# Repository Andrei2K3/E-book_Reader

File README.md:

# OpenBook Project - README

This repository contains the hardware, manufacturing, mechanical, and documentation files for **OpenBook**, a low-cost, open-source e-book reader built around the **ESP32-C6** microcontroller.

---

## Overview

The OpenBook is a low-power, open-source e-book reader designed around the ESP32-C6 microcontroller. Featuring Wi-Fi 6 and Bluetooth LE, it uses a large 7.5-inch e-paper display to achieve excellent readability and battery performance.

This document includes the system block diagram, hardware pinout, BOM, component links, design log, and licensing.

---

## System Block Diagram

---

## Bill of Materials (BOM)

| Name of component | Device                                       | Check Prices                                                                                                | DataSheet                                                                                                 |
|-------------------|----------------------------------------------|-----------------------------------------------------------------------------------------------------------------|---------------------------------------------------------------------------------------------------------------|
| U1                | W25Q512JVEIQ                                 | https://www.snapeda.com/parts/W25Q512JVEIQ/Winbond+Electronics/view-part/?ref=eda                             | https://www.snapeda.com/parts/W25Q512JVEIQ/Winbond+Electronics/view-part/?ref=eda                             |
| U2                | ESP32-C6-WROOM-1-N8                          | https://www.snapeda.com/parts/ESP32-C6-WROOM-1-N8/Espressif+Systems/view-part/?ref=eda                        | https://www.snapeda.com/parts/ESP32-C6-WROOM-1-N8/Espressif+Systems/view-part/?ref=eda                        |
| U3                | DS3231SN#                                    | https://www.snapeda.com/parts/DS3231SN%23/Analog+Devices/view-part/?ref=eda                                   | https://www.snapeda.com/parts/DS3231SN%23/Analog+Devices/view-part/?ref=eda                                   |
| U4                | MAX17048G+T10                                | https://www.snapeda.com/parts/MAX17048G+T10/Analog+Devices/view-part/?ref=eda                                 | https://www.snapeda.com/parts/MAX17048G+T10/Analog+Devices/view-part/?ref=eda                                 |
| U5                | ESP32_WROVER_SPARKFUN-IC-POWER_MCP73831      | https://eu.mouser.com/ProductDetail/Microchip-Technology/MCP73831T-2ACI-OT?qs=yUQqVecv4qvbBQBGbHx0Mw%3D%3Dcf   | https://eu.mouser.com/ProductDetail/Microchip-Technology/MCP73831T-2ACI-OT?qs=yUQqVecv4qvbBQBGbHx0Mw%3D%3Dcf   |
| BOOT_BUTTON       | BUTTON_CUSYOMV1                             | https://industry.panasonic.com/global/en/products/control/switch/light-touch/number/evqpuj02k                  | https://industry.panasonic.com/global/en/products/control/switch/light-touch/number/evqpuj02k                  |
| CHANGE_BUTTON     | BUTTON_CUSYOMV1                             | https://industry.panasonic.com/global/en/products/control/switch-light-touch/number/evqpuj02k                  | https://industry.panasonic.com/global/en/products/control/switch-light-touch/number/evqpuj02k                  |
| RESET_BUTTON      | BUTTON_CUSYOMV1                             | https://industry.panasonic.com/global/en/products/control/switch/light-touch/number/evqpuj02k                  | https://industry.panasonic.com/global/en/products/control/switch/light-touch/number/evqpuj02k                  |
| Q1                | ESP32_WROVER_SPARKFUN-DISCRETESEMI_MOSFET_...| https://componentsearchengine.com/part-view/DMG2305UX-7/Diodes%20Incorporated                                  | https://componentsearchengine.com/part-view/DMG2305UX-7/Diodes%20Incorporated                                  |
| Q2                | ESP32_WROVER_SPARKFUN-DISCRETESEMI_MOSFET_...| https://componentsearchengine.com/part-view/DMG2305UX-7/Diodes%20Incorporated                                  | https://componentsearchengine.com/part-view/DMG2305UX-7/Diodes%20Incorporated                                  |
| Q3                | D8                                           | https://componentsearchengine.com/part-view/SI1308EDL-T1-GE3/Vishay                                           | https://componentsearchengine.com/part-view/SI1308EDL-T1-GE3/Vishay                                           |
| PFMF.050.1        | ESP32C6_VARISTORCN1812                       | https://www.mouser.co.uk/ProductDetail/EPCOS-TDK/B72520T0350K062?qs=dEfas%2FXlABIszF52uu7vrg%3D%3D              | https://www.mouser.co.uk/ProductDetail/EPCOS-TDK/B72520T0350K062?qs=dEfas%2FXlABIszF52uu7vrg%3D%3D              |
| IC1               | BD5229G-TR                                   | https://componentsearchengine.com/part-view/BD5229G-TR/ROHM%20Semiconductor                                    | https://componentsearchengine.com/part-view/BD5229G-TR/ROHM%20Semiconductor                                    |
| IC4               | XC6220A331MR-G                               | https://componentsearchengine.com/part-view/XC6220A331MR-G/Torex                                              | https://componentsearchengine.com/part-view/XC6220A331MR-G/Torex                                              |
| J1                | FH34SRJ-24S-0.5SH_99_                        | https://componentsearchengine.com/part-view/XC6220A331MR-G/Torex                                              | https://componentsearchengine.com/part-view/XC6220A331MR-G/Torex                                              |
| J2                | SAMACSYS_PARTS_USB4110-GF-A                  | https://componentsearchengine.com/part-view/USB4110-GF-A/GCT%20(GLOBAL%20CONNECTOR%20TECHNOLOGY               | https://componentsearchengine.com/part-view/USB4110-GF-A/GCT%20(GLOBAL%20CONNECTOR%20TECHNOLOGY               |
| J3                | QWIIC_CONNECTORJS-1MM                        | https://componentsearchengine.com/part-view/USB4110-GF-A/GCT%20(GLOBAL%20CONNECTOR%20TECHNOLOGY               | https://componentsearchengine.com/part-view/USB4110-GF-A/GCT%20(GLOBAL%20CONNECTOR%20TECHNOLOGY               |
| J4                | 112A-TAAR-R03_ATTEND                         | https://store.comet.srl.ro/Catalogue/Product/43497/                                                            | https://store.comet.srl.ro/Catalogue/Product/43497/                                                            |
| L1                | 744043680IND_4828-WE-TPC_WRE                 | https://eu.mouser.com/ProductDetail/Wurth-Elektronik/744043680?qs=PGXP4M47uW6VkZq%252BkzjrHA%3D%3D               | https://eu.mouser.com/ProductDetail/Wurth-Elektronik/744043680?qs=PGXP4M47uW6VkZq%252BkzjrHA%3D%3D               |
| SENSOR2           | ESP32_WROVER_BME680_BME680                   | https://www.snapeda.com/parts/BME680/Bosch/view-part/?welcome=home                                            | https://www.snapeda.com/parts/BME680/Bosch/view-part/?welcome=home                                            |
| SJ1              | SJ                                           | https://grabcad.com/library/solder-jumpers-1                                                                   | https://grabcad.com/library/solder-jumpers-1                                                                   |
| C1                | ESP32_WROVER_EAGLE-LTSPICE_CC0402            | https://industry.panasonic.com/global/en/products/control/switch/light-touch/number/evqpuj02k                  | https://industry.panasonic.com/global/en/products/control/switch/light-touch/number/evqpuj02k                  |
| C1_BAT            | ESP32_WROVER_EAGLE-LTSPICE_CC0402            | https://industry.panasonic.com/global/en/products/control/switch/light-touch/number/evqpuj02k                  | https://industry.panasonic.com/global/en/products/control/switch/light-touch/number/evqpuj02k                  |
| C1_BAT1           | EAGLE-LTSPICE_CC0402                         | https://industry.panasonic.com/global/en/products/control/switch/light-touch/number/evqpuj02k                  | https://industry.panasonic.com/global/en/products/control/switch/light-touch/number/evqpuj02k                  |
| C1_BAT2           | EAGLE-LTSPICE_CC0402                         | https://industry.panasonic.com/global/en/products/control/switch/light-touch/number/evqpuj02k                  | https://industry.panasonic.com/global/en/products/control/switch/light-touch/number/evqpuj02k                  |
| C2                | ESP32_WROVER_EAGLE-LTSPICE_CC0402            | https://industry.panasonic.com/global/en/products/control/switch/light-touch/number/evqpuj02k                  | https://industry.panasonic.com/global/en/products/control/switch/light-touch/number/evqpuj02k                  |
| C2_BAT\           | ESP32_WROVER_EAGLE-LTSPICE_CC0402            | https://industry.panasonic.com/global/en/products/control/switch/light-touch/number/evqpuj02k                  | https://industry.panasonic.com/global/en/products/control/switch/light-touch/number/evqpuj02k                  |
| C3                | RCL_CPOL-EUCT3528                            | https://industry.panasonic.com/global/en/products/control/switch/light-touch/number/evqpuj02k                  | https://industry.panasonic.com/global/en/products/control/switch/light-touch/number/evqpuj02k                  |
| C4                | ESP32_WROVER_EAGLE-LTSPICE_CC0402            | https://industry.panasonic.com/global/en/products/control/switch/light-touch/number/evqpuj02k                  | https://industry.panasonic.com/global/en/products/control/switch/light-touch/number/evqpuj02k                  |
| C4_USB            | ESP32_WROVER_EAGLE-LTSPICE_CC0402            | https://industry.panasonic.com/global/en/products/control/switch/light-touch/number/evqpuj02k                  | https://industry.panasonic.com/global/en/products/control/switch/light-touch/number/evqpuj02k                  |
| C5                | ESP32_WROVER_EAGLE-LTSPICE_CC0402            | https://industry.panasonic.com/global/en/products/control/switch/light-touch/number/evqpuj02k                  | https://industry.panasonic.com/global/en/products/control/switch/light-touch/number/evqpuj02k                  |
| C5_USB            | ESP32_WROVER_EAGLE-LTSPICE_CC0402            | https://industry.panasonic.com/global/en/products/control/switch/light-touch/number/evqpuj02k                  | https://industry.panasonic.com/global/en/products/control/switch/light-touch/number/evqpuj02k                  |
| C6                | ESP32_WROVER_EAGLE-LTSPICE_CC0402            | https://industry.panasonic.com/global/en/products/control/switch/light-touch/number/evqpuj02k                  | https://industry.panasonic.com/global/en/products/control/switch/light-touch/number/evqpuj02k                  |
| C7                | ESP32_WROVER_EAGLE-LTSPICE_CC0402            | https://industry.panasonic.com/global/en/products/control/switch/light-touch/number/evqpuj02k                  | https://industry.panasonic.com/global/en/products/control/switch/light-touch/number/evqpuj02k                  |
| C8                | ESP32_WROVER_EAGLE-LTSPICE_CC0402            | https://industry.panasonic.com/global/en/products/control/switch/light-touch/number/evqpuj02k                  | https://industry.panasonic.com/global/en/products/control/switch/light-touch/number/evqpuj02k                  |
| C9                | EAGLE-LTSPICE_CC0402                         | https://industry.panasonic.com/global/en/products/control/switch/light-touch/number/evqpuj02k                  | https://industry.panasonic.com/global/en/products/control/switch/light-touch/number/evqpuj02k                  |
| C10               | ESP32_WROVER_EAGLE-LTSPICE_CC0402            | https://industry.panasonic.com/global/en/products/control/switch/light-touch/number/evqpuj02k                  | https://industry.panasonic.com/global/en/products/control/switch/light-touch/number/evqpuj02k                  |
| C10_SUPERCAP      | CPH3225A                                     | https://www.snapeda.com/parts/CPH3225A/Seiko+Instruments/view-part/?ref=eda                                   | https://www.snapeda.com/parts/CPH3225A/Seiko+Instruments/view-part/?ref=eda                                   |
| CHG_LED           | ADAFRUIT_LEDCHIP-LED0603                     | https://www.snapeda.com/parts/KP-1608SURCK/Kingbright/view-part/?ref=search&t=LED%200603                       | https://www.snapeda.com/parts/KP-1608SURCK/Kingbright/view-part/?ref=search&t=LED%200603                       |
| C_DELAY           | ESP32_WROVER_EAGLE-LTSPICE_CC0402            | https://industry.panasonic.com/global/en/products/control/switch/light-touch/number/evqpuj02k                  | https://industry.panasonic.com/global/en/products/control/switch/light-touch/number/evqpuj02k                  |
| D1                | USBLC6-2SC6Y                                 | https://www.snapeda.com/parts/USBLC6-2SC6Y/STMicroelectronics/view-part/?ref=eda                              | https://www.snapeda.com/parts/USBLC6-2SC6Y/STMicroelectronics/view-part/?ref=eda                              |
| D2                | ESP32_WROVER_AVX---SD0805S020S1R0_AVX_...    | https://eu.mouser.com/ProductDetail/KYOCERA-AVX/SD0805S020S1R0?qs=jCA%252BPfw4LHbpkAoSnwrdjw%3D%3D              | http://datasheets.avx.com/schottky.pdf                                                                         |
| D3                | MBR0530                                      | https://eu.mouser.com/ProductDetail/KYOCERA-AVX/SD0805S020S1R0?qs=jCA%252BPfw4LHbpkAoSnwrdjw%3D%3D              | https://eu.mouser.com/ProductDetail/KYOCERA-AVX/SD0805S020S1R0?qs=jCA%252BPfw4LHbpkAoSnwrdjw%3D%3D              |
| D4                | MBR0530                                      | https://www.snapeda.com/parts/MBR0530/Onsemi/view-part/?ref=eda                                                | https://www.snapeda.com/parts/MBR0530/Onsemi/view-part/?ref=eda                                                |
| D5                | MBR0530                                      | https://www.snapeda.com/parts/MBR0530/Onsemi/view-part/?ref=eda                                                | https://www.snapeda.com/parts/MBR0530/Onsemi/view-part/?ref=eda                                                |
| D6                | PGB1010603MR                                 | https://www.snapeda.com/parts/PGB1010603MR/Littelfuse/view-part/?ref=eda                                      | https://www.snapeda.com/parts/PGB1010603MR/Littelfuse/view-part/?ref=eda                                      |
| D7                | ESP32_WROVER_AVX---SD0805S020S1R0_AVX_...    | https://eu.mouser.com/ProductDetail/KYOCERA-AVX/SD0805S020S1R0?qs=jCA%252BPfw4LHbpkAoSnwrdjw%3D%3D              | http://datasheets.avx.com/schottky.pdf                                                                         |
| D8                | PGB1010603MR                                 | https://www.snapeda.com/parts/PGB1010603MR/Littelfuse/view-part/?ref=eda                                      | https://www.snapeda.com/parts/PGB1010603MR/Littelfuse/view-part/?ref=eda                                      |
| D9                | PGB1010603MR                                 | https://www.snapeda.com/parts/PGB1010603MR/Littelfuse/view-part/?ref=eda                                      | https://www.snapeda.com/parts/PGB1010603MR/Littelfuse/view-part/?ref=eda                                      |
| D10               | PGB1010603MR                                 | https://www.snapeda.com/parts/PGB1010603MR/Littelfuse/view-part/?ref=eda                                      | https://www.snapeda.com/parts/PGB1010603MR/Littelfuse/view-part/?ref=eda                                      |
| D11               | PGB1010603MR                                 | https://www.snapeda.com/parts/PGB1010603MR/Littelfuse/view-part/?ref=eda                                      | https://www.snapeda.com/parts/PGB1010603MR/Littelfuse/view-part/?ref=eda                                      |
| D12               | PGB1010603MR                                 | https://www.snapeda.com/parts/PGB1010603MR/Littelfuse/view-part/?ref=eda                                      | https://www.snapeda.com/parts/PGB1010603MR/Littelfuse/view-part/?ref=eda                                      |
| EPD_C1            | ESP32_WROVER_EAGLE-LTSPICE_CC0402            | https://industry.panasonic.com/global/en/products/control/switch/light-touch/number/evqpuj02k                  | https://industry.panasonic.com/global/en/products/control/switch/light-touch/number/evqpuj02k                  |
| EPD_C2            | ESP32_WROVER_EAGLE-LTSPICE_CC0402            | https://industry.panasonic.com/global/en/products/control/switch/light-touch/number/evqpuj02k                  | https://industry.panasonic.com/global/en/products/control/switch/light-touch/number/evqpuj02k                  |
| EPD_C5            | ESP32_WROVER_EAGLE-LTSPICE_CC0402            | https://industry.panasonic.com/global/en/products/control/switch/light-touch/number/evqpuj02k                  | https://industry.panasonic.com/global/en/products/control/switch/light-touch/number/evqpuj02k                  |
| EPD_C6            | ESP32_WROVER_EAGLE-LTSPICE_CC0402            | https://industry.panasonic.com/global/en/products/control/switch/light-touch/number/evqpuj02k                  | https://industry.panasonic.com/global/en/products/control/switch/light-touch/number/evqpuj02k                  |
| EPD_C7            | ESP32_WROVER_EAGLE-LTSPICE_CC0402            | https://industry.panasonic.com/global/en/products/control/switch/light-touch/number/evqpuj02k                  | https://industry.panasonic.com/global/en/products/control/switch/light-touch/number/evqpuj02k                  |
| EPD_C8            | ESP32_WROVER_EAGLE-LTSPICE_CC0402            | https://industry.panasonic.com/global/en/products/control/switch/light-touch/number/evqpuj02k                  | https://industry.panasonic.com/global/en/products/control/switch/light-touch/number/evqpuj02k                  |
| EPD_C9            | ESP32_WROVER_EAGLE-LTSPICE_CC0402            | https://industry.panasonic.com/global/en/products/control/switch/light-touch/number/evqpuj02k                  | https://industry.panasonic.com/global/en/products/control/switch/light-touch/number/evqpuj02k                  |
| EPD_C10           | ESP32_WROVER_EAGLE-LTSPICE_CC0402            | https://industry.panasonic.com/global/en/products/control/switch/light-touch/number/evqpuj02k                  | https://industry.panasonic.com/global/en/products/control/switch/light-touch/number/evqpuj02k                  |
| EPD_C11           | ESP32_WROVER_EAGLE-LTSPICE_CC0402            | https://industry.panasonic.com/global/en/products/control/switch/light-touch/number/evqpuj02k                  | https://industry.panasonic.com/global/en/products/control/switch/light-touch/number/evqpuj02k                  |
| EPD_C12           | ESP32_WROVER_EAGLE-LTSPICE_CC0402            | https://industry.panasonic.com/global/en/products/control/switch/light-touch/number/evqpuj02k                  | https://industry.panasonic.com/global/en/products/control/switch/light-touch/number/evqpuj02k                  |
| R1                | ESP32_WROVER_EAGLE-LTSPICE_RR0402            | https://componentsearchengine.com/part-view/R0402%201%25%20100%20K%20(RC0402FR-07100KL                         | https://componentsearchengine.com/part-view/R0402%201%25%20100%20K%20(RC0402FR-07100KL                         |
| R1-PINH           | ESP32_WROVER_EAGLE-LTSPICE_RR0402            | https://componentsearchengine.com/part-view/R0402%201%25%20100%20K%20(RC0402FR-07100KL                         | https://componentsearchengine.com/part-view/R0402%201%25%20100%20K%20(RC0402FR-07100KL                         |
| R1-PINH1          | ESP32_WROVER_EAGLE-LTSPICE_RR0402            | https://componentsearchengine.com/part-view/R0402%201%25%20100%20K%20(RC0402FR-07100KL                         | https://componentsearchengine.com/part-view/R0402%201%25%20100%20K%20(RC0402FR-07100KL                         |
| R1_BAT            | ESP32_WROVER_EAGLE-LTSPICE_RR0402            | https://componentsearchengine.com/part-view/R0402%201%25%20100%20K%20(RC0402FR-07100KL                         | https://componentsearchengine.com/part-view/R0402%201%25%20100%20K%20(RC0402FR-07100KL                         |
| R1_PWRUSB         | ESP32_WROVER_EAGLE-LTSPICE_RR0402            | https://componentsearchengine.com/part-view/R0402%201%25%20100%20K%20(RC0402FR-07100KL                         | https://componentsearchengine.com/part-view/R0402%201%25%20100%20K%20(RC0402FR-07100KL                         |
| R2                | ESP32_WROVER_EAGLE-LTSPICE_RR0402            | https://componentsearchengine.com/part-view/R0402%201%25%20100%20K%20(RC0402FR-07100KL                         | https://componentsearchengine.com/part-view/R0402%201%25%20100%20K%20(RC0402FR-07100KL                         |
| R2-PINH           | ESP32_WROVER_EAGLE-LTSPICE_RR0402            | https://componentsearchengine.com/part-view/R0402%201%25%20100%20K%20(RC0402FR-07100KL                         | https://componentsearchengine.com/part-view/R0402%201%25%20100%20K%20(RC0402FR-07100KL                         |
| R2-PINH1          | ESP32_WROVER_EAGLE-LTSPICE_RR0402            | https://componentsearchengine.com/part-view/R0402%201%25%20100%20K%20(RC0402FR-07100KL                         | https://componentsearchengine.com/part-view/R0402%201%25%20100%20K%20(RC0402FR-07100KL                         |
| R2-USB            | ESP32_WROVER_EAGLE-LTSPICE_RR0402            | https://componentsearchengine.com/part-view/R0402%201%25%20100%20K%20(RC0402FR-07100KL                         | https://componentsearchengine.com/part-view/R0402%201%25%20100%20K%20(RC0402FR-07100KL                         |
| R2-USB1           | ESP32_WROVER_EAGLE-LTSPICE_RR0402            | https://componentsearchengine.com/part-view/R0402%201%25%20100%20K%20(RC0402FR-07100KL                         | https://componentsearchengine.com/part-view/R0402%201%25%20100%20K%20(RC0402FR-07100KL                         |
| R2_BAT            | ESP32_WROVER_EAGLE-LTSPICE_RR0402            | https://componentsearchengine.com/part-view/R0402%201%25%20100%20K%20(RC0402FR-07100KL                         | https://componentsearchengine.com/part-view/R0402%201%25%20100%20K%20(RC0402FR-07100KL                         |
| R3                | ESP32_WROVER_EAGLE-LTSPICE_RR0402            | https://componentsearchengine.com/part-view/R0402%201%25%20100%20K%20(RC0402FR-07100KL                         | https://componentsearchengine.com/part-view/R0402%201%25%20100%20K%20(RC0402FR-07100KL                         |
| R4                | ESP32_WROVER_EAGLE-LTSPICE_RR0402            | https://componentsearchengine.com/part-view/R0402%201%25%20100%20K%20(RC0402FR-07100KL                         | https://componentsearchengine.com/part-view/R0402%201%25%20100%20K%20(RC0402FR-07100KL                         |
| R5                | ESP32_WROVER_EAGLE-LTSPICE_RR0402            | https://componentsearchengine.com/part-view/R0402%201%25%20100%20K%20(RC0402FR-07100KL                         | https://componentsearchengine.com/part-view/R0402%201%25%20100%20K%20(RC0402FR-07100KL                         |
| R6                | ESP32_WROVER_EAGLE-LTSPICE_RR0402            | https://componentsearchengine.com/part-view/R0402%201%25%20100%20K%20(RC0402FR-07100KL                         | https://componentsearchengine.com/part-view/R0402%201%25%20100%20K%20(RC0402FR-07100KL                         |
| R7                | ESP32_WROVER_EAGLE-LTSPICE_RR0402            | https://componentsearchengine.com/part-view/R0402%201%25%20100%20K%20(RC0402FR-07100KL                         | https://componentsearchengine.com/part-view/R0402%201%25%20100%20K%20(RC0402FR-07100KL                         |
| R8                | ESP32_WROVER_EAGLE-LTSPICE_RR0402            | https://componentsearchengine.com/part-view/R0402%201%25%20100%20K%20(RC0402FR-07100KL                         | https://componentsearchengine.com/part-view/R0402%201%25%20100%20K%20(RC0402FR-07100KL                         |
| R9                | ESP32_WROVER_EAGLE-LTSPICE_RR0402            | https://componentsearchengine.com/part-view/R0402%201%25%20100%20K%20(RC0402FR-07100KL                         | https://componentsearchengine.com/part-view/R0402%201%25%20100%20K%20(RC0402FR-07100KL                         |
| R10               | ESP32_WROVER_EAGLE-LTSPICE_RR0402            | https://componentsearchengine.com/part-view/R0402%201%25%20100%20K%20(RC0402FR-07100KL                         | https://componentsearchengine.com/part-view/R0402%201%25%20100%20K%20(RC0402FR-07100KL                         |
| R_BOOT            | ESP32_WROVER_EAGLE-LTSPICE_RR0402            | https://componentsearchengine.com/part-view/R0402%201%25%20100%20K%20(RC0402FR-07100KL                         | https://componentsearchengine.com/part-view/R0402%201%25%20100%20K%20(RC0402FR-07100KL                         |
| R_CAPACITOR       | ESP32_WROVER_EAGLE-LTSPICE_RR0402            | https://componentsearchengine.com/part-view/R0402%201%25%20100%20K%20(RC0402FR-07100KL                         | https://componentsearchengine.com/part-view/R0402%201%25%20100%20K%20(RC0402FR-07100KL                         |
| R_CHANGE          | ESP32_WROVER_EAGLE-LTSPICE_RR0402            | https://componentsearchengine.com/part-view/R0402%201%25%20100%20K%20(RC0402FR-07100KL                         | https://componentsearchengine.com/part-view/R0402%201%25%20100%20K%20(RC0402FR-07100KL                         |
| R_CL1             | ESP32_WROVER_EAGLE-LTSPICE_RR0402            | https://componentsearchengine.com/part-view/R0402%201%25%20100%20K%20(RC0402FR-07100KL                         | https://componentsearchengine.com/part-view/R0402%201%25%20100%20K%20(RC0402FR-07100KL                         |
| R_RESET           | ESP32_WROVER_EAGLE-LTSPICE_RR0402            | https://componentsearchengine.com/part-view/R0402%201%25%20100%20K%20(RC0402FR-07100KL                         | https://componentsearchengine.com/part-view/R0402%201%25%20100%20K%20(RC0402FR-07100KL                         |
| TP1               | TPTP20R                                      | -                                                                                                            | -                                                                                                           |
| TP2               | TPTP20R                                      | -                                                                                                            | -                                                                                                           |
| TP3               | TPTP20R                                      | -                                                                                                            | -                                                                                                           |
| TP4               | TPTP20R                                      | -                                                                                                            | -                                                                                                           |
| TP5               | TPTP20R                                      | -                                                                                                            | -                                                                                                           |
| TP6               | TPTP20R                                      | -                                                                                                            | -                                                                                                           |
| TP7               | TPTP20R                                      | -                                                                                                            | -                                                                                                           |
| TP8               | TPTP20R                                      | -                                                                                                            | -                                                                                                           |
| TP9               | TPTP20R                                      | -                                                                                                            | -                                                                                                           |
| TP10              | TPTP20R                                      | -                                                                                                            | -                                                                                                           |
| TP11              | TPTP20R                                      | -                                                                                                            | -                                                                                                           |
| TP12              | TPTP20R                                      | -                                                                                                            | -                                                                                                           |
| TP13              | TPTP20R                                      | -                                                                                                            | -                                                                                                           |
| TP14              | TPTP20R                                      | -                                                                                                            | -                                                                                                           |
| TP15              | TPTP20R                                      | -                                                                                                            | -                                                                                                           |
| TP16              | TPTP20R                                      | -                                                                                                            | -                                                                                                           |
| TP17              | TPTP20R                                      | -                                                                                                            | -                                                                                                           |

---

## Main Hardware Components

# ESP32-C6 Microcontroller

- Architecture: 32-bit RISC-V core operating up to 160 MHz
- Communication: Built-in Wi-Fi 6, Bluetooth 5 LE, and USB 2.0 interface
- RAM & Storage: 512KB SRAM onboard, paired with 8MB external flash
- Power Efficiency: Equipped with advanced low-power and sleep modes
- I/O Capabilities: Supports SPI, I²C, UART, and multiple GPIOs

# SD Card Slot

- Storage Role: Enables additional memory for e-books, logs, and firmware
- Interface Options: Compatible with both SPI and native SD protocols

# External Memory

- Type: Serial NOR Flash, model W25Q512JVEIQ
- Capacity: Provides 8MB for firmware storage and high-volume data

# E-Paper Display

- Dimensions & Quality: 7.5-inch diagonal, 800×480 resolution
- Energy Profile: Consumes power only during updates; remains static otherwise
- Data Transfer: Communicates using a 4-wire SPI interface

# USB-C Interface

- Primary Roles: Allows battery charging, data transfer, and firmware updates
- Electrical Safety: Integrated ESD protection and compliant terminations
- Update Support: Enables both USB-based and OTA software upgrades

# Power Management

- Energy Source: Uses a 2500mAh 3.7V Li-Po rechargeable battery
- Monitoring Features: Battery state tracked via MAX17048 fuel gauge (I²C)
- Charging Circuitry: Based on MCP73831 controller via USB-C input
- Voltage Regulation: Supplies a clean 3.3V rail using an LDO such as XC6220

# Environmental Sensor

- Sensor Type: BME688 integrated environmental sensor
- Measured Parameters: Ambient temperature, relative humidity, atmospheric pressure, and air quality (VOC/eCO2)
- Communication: I²C protocol at 400kHz

# Input Controls

- Functional Use: Facilitates navigation, menu interaction, and device reset

---

## Communication Interfaces Overview

# USB

- Provides both power input and data communication via the USB-C port.
- Supports firmware flashing and charging through a single interface.

# I²C Bus

- Used to interface with low-speed peripherals such as:
    - Environmental sensor (BME688)
    - Battery monitoring chip (MAX17048)
    - RT Clock (DS3231)
    - Qwiic-compatible expansion modules

# General Purpose I/O (GPIO)

- Dedicated digital inputs for tactile button controls (3x)
- Additional control signals for peripherals, such as:
    - Display reset
    - E-paper busy status monitoring
    - Power control or wake signals

# SPI Interface

- Standard 4-wire SPI used for driving the e-paper display

---

## Estimated Power Consumption

This section provides an overview of the average power consumption for each hardware component in the OpenBook E-Reader during both active use and sleep modes.

| Component                   | Active Mode Consumption | Sleep / Idle Consumption     | Notes                                                                 |
|----------------------------|--------------------------|-------------------------------|-----------------------------------------------------------------------|
| **ESP32-C6 MCU**           | 80–150 mA                | < 50 µA (deep sleep)          | Includes Wi-Fi processing and peripheral control                     |
| **7.5” E-Paper Display**   | ~30–40 mA (during refresh) | ~1 µA (static image retained) | Power only consumed during screen updates                            |
| **BME688 Sensor**          | ~2.1 mA                  | < 1 µA (standby mode)         | Used for environmental data collection (temp/humidity/air quality)   |
| **DS3231 RTC**             | —                        | ~2 µA                         | Always running to keep accurate time                                 |
| **MAX17048 Fuel Gauge**    | ~50 µA                   | ~50 µA                        | Monitors battery level continuously                                  |
| **MCP73831 Charging IC**   | Up to 1A (when charging) | 0 µA (when idle)              | Controlled via USB VBUS connection                                   |
| **Buttons (3x)**           | 0 mA (passive)           | 0 mA                          | Use GPIO input pull-downs; no active consumption                     |
| **SD Card (optional)**     | 10–30 mA (read/write)    | 0 mA (unmounted)              | Used only during eBook loading or logging                            |
| **USB Peripherals**        | Varies (USB Host mode)   | 0 mA                          | Only active when data transfer is in use                             |

### Total Estimated Consumption

| Usage Scenario                | Estimated Total Current |
|------------------------------|-------------------------|
| **Full Active Reading**      | ~120–170 mA             |
| **Wi-Fi + Sensor Polling**   | ~100–130 mA             |
| **Partial Sleep (Wi-Fi Off)**| ~5–10 mA                |
| **Deep Sleep (RTC only)**    | ~100–150 µA             |

### Battery Life Estimation

Given a 2500 mAh 3.7V Li-Po battery:

- **Active Reading 2 hours/day** → ~7–10 days battery life
- **Standby Mode Only** → up to **1 month**
- **Mixed Use (Wi-Fi, sensors, display refreshes)** → 5–7 days typical

These values are estimations and will vary depending on usage patterns, Wi-Fi activity, and environmental sensor polling intervals.

---

## ESP32-C6 Pin Mapping

This table shows the actual GPIO-to-function mapping as used in the OpenBook E-Reader, based on the schematic of the ESP32-C6-WROOM-1-N8 module provided.

| GPIO      | Label in Schematic | Function Description                        | Peripheral / Role                     |
|-----------|---------------------|---------------------------------------------|---------------------------------------|
| **GPIO9** | IO0 / BOOT          | Boot select button                          | Used for entering UART download mode |
| **GPIO4** | SS_SD               | SPI Chip Select for SD card                 | microSD card                          |
| **GPIO6** | SCK                 | SPI Clock                                   | Shared SPI (e-Paper + SD)            |
| **GPIO7** | MOSI                | SPI Data Out                                | Shared SPI (e-Paper + SD)            |
| **GPIO2** | MISO                | SPI Data In                                 | SD card only                          |
| **GPIO5** | EPD_DC              | Data/Command pin for e-paper display        | e-Paper display                       |
| **GPIO10** | EPD_CS              | Chip Select for e-paper display             | e-Paper display                       |
| **GPIO3** | EPD_BUSY            | Busy pin input from e-paper display         | e-Paper display                       |
| **GPIO11** | FLASH_CS            | Flash chip select (internal flash)          | Reserved – do not use externally     |
| **GPIO13**| USB D+              | USB 2.0 Full Speed Data+                    | USB-C Interface                       |
| **GPIO12**| USB D-              | USB 2.0 Full Speed Data-                    | USB-C Interface                       |
| **GPIO16**| TX                  | UART TX (console/debug)                     | Optional serial logging               |
| **GPIO17**| RX                  | UART RX (console/debug)                     | Optional serial logging               |
| **GPIO18**| RTC_RST             | RTC reset                                   | DS3231 (RTC)                          |
| **GPIO0**| INT_RTC             | RTC interrupt/alarm                         | DS3231 optional alarm/interrupt       |
| **GPIO21**| SDA                 | I2C Data Line                                | Shared between RTC, BME688, MAX17048 |
| **GPIO22**| SCL                 | I2C Clock Line                               | Shared between RTC, BME688, MAX17048 |
| **GPIO20**| EPD_3V3_C           | Power control / enable for e-paper display  | Can be used for low-power control     |
| **GPIO23**| EPD_RST    | Redundant label for GPIO8                   | See GPIO8 (same net)                  |

---

# PCB Design and Mechanical Integration

The OpenBook PCB has been designed as a compact, two-layer board with careful attention to power integrity, signal routing, and EMI minimization. Components are placed for thermal efficiency and optimal antenna performance.
- The /Hardware directory contains the original KiCad schematic (.sch) and PCB layout (.brd) files for further modification or inspection.
- High-quality 3D renderings of the PCB and complete device are available in the /Images folder.
- 3D models of the enclosure, including exploded views and Fusion 360 assemblies, can be found in /Mechanical.
- The /Manufacturing folder includes production-ready files such as Gerbers, BOM and Pick & Place data for automated assembly.

---

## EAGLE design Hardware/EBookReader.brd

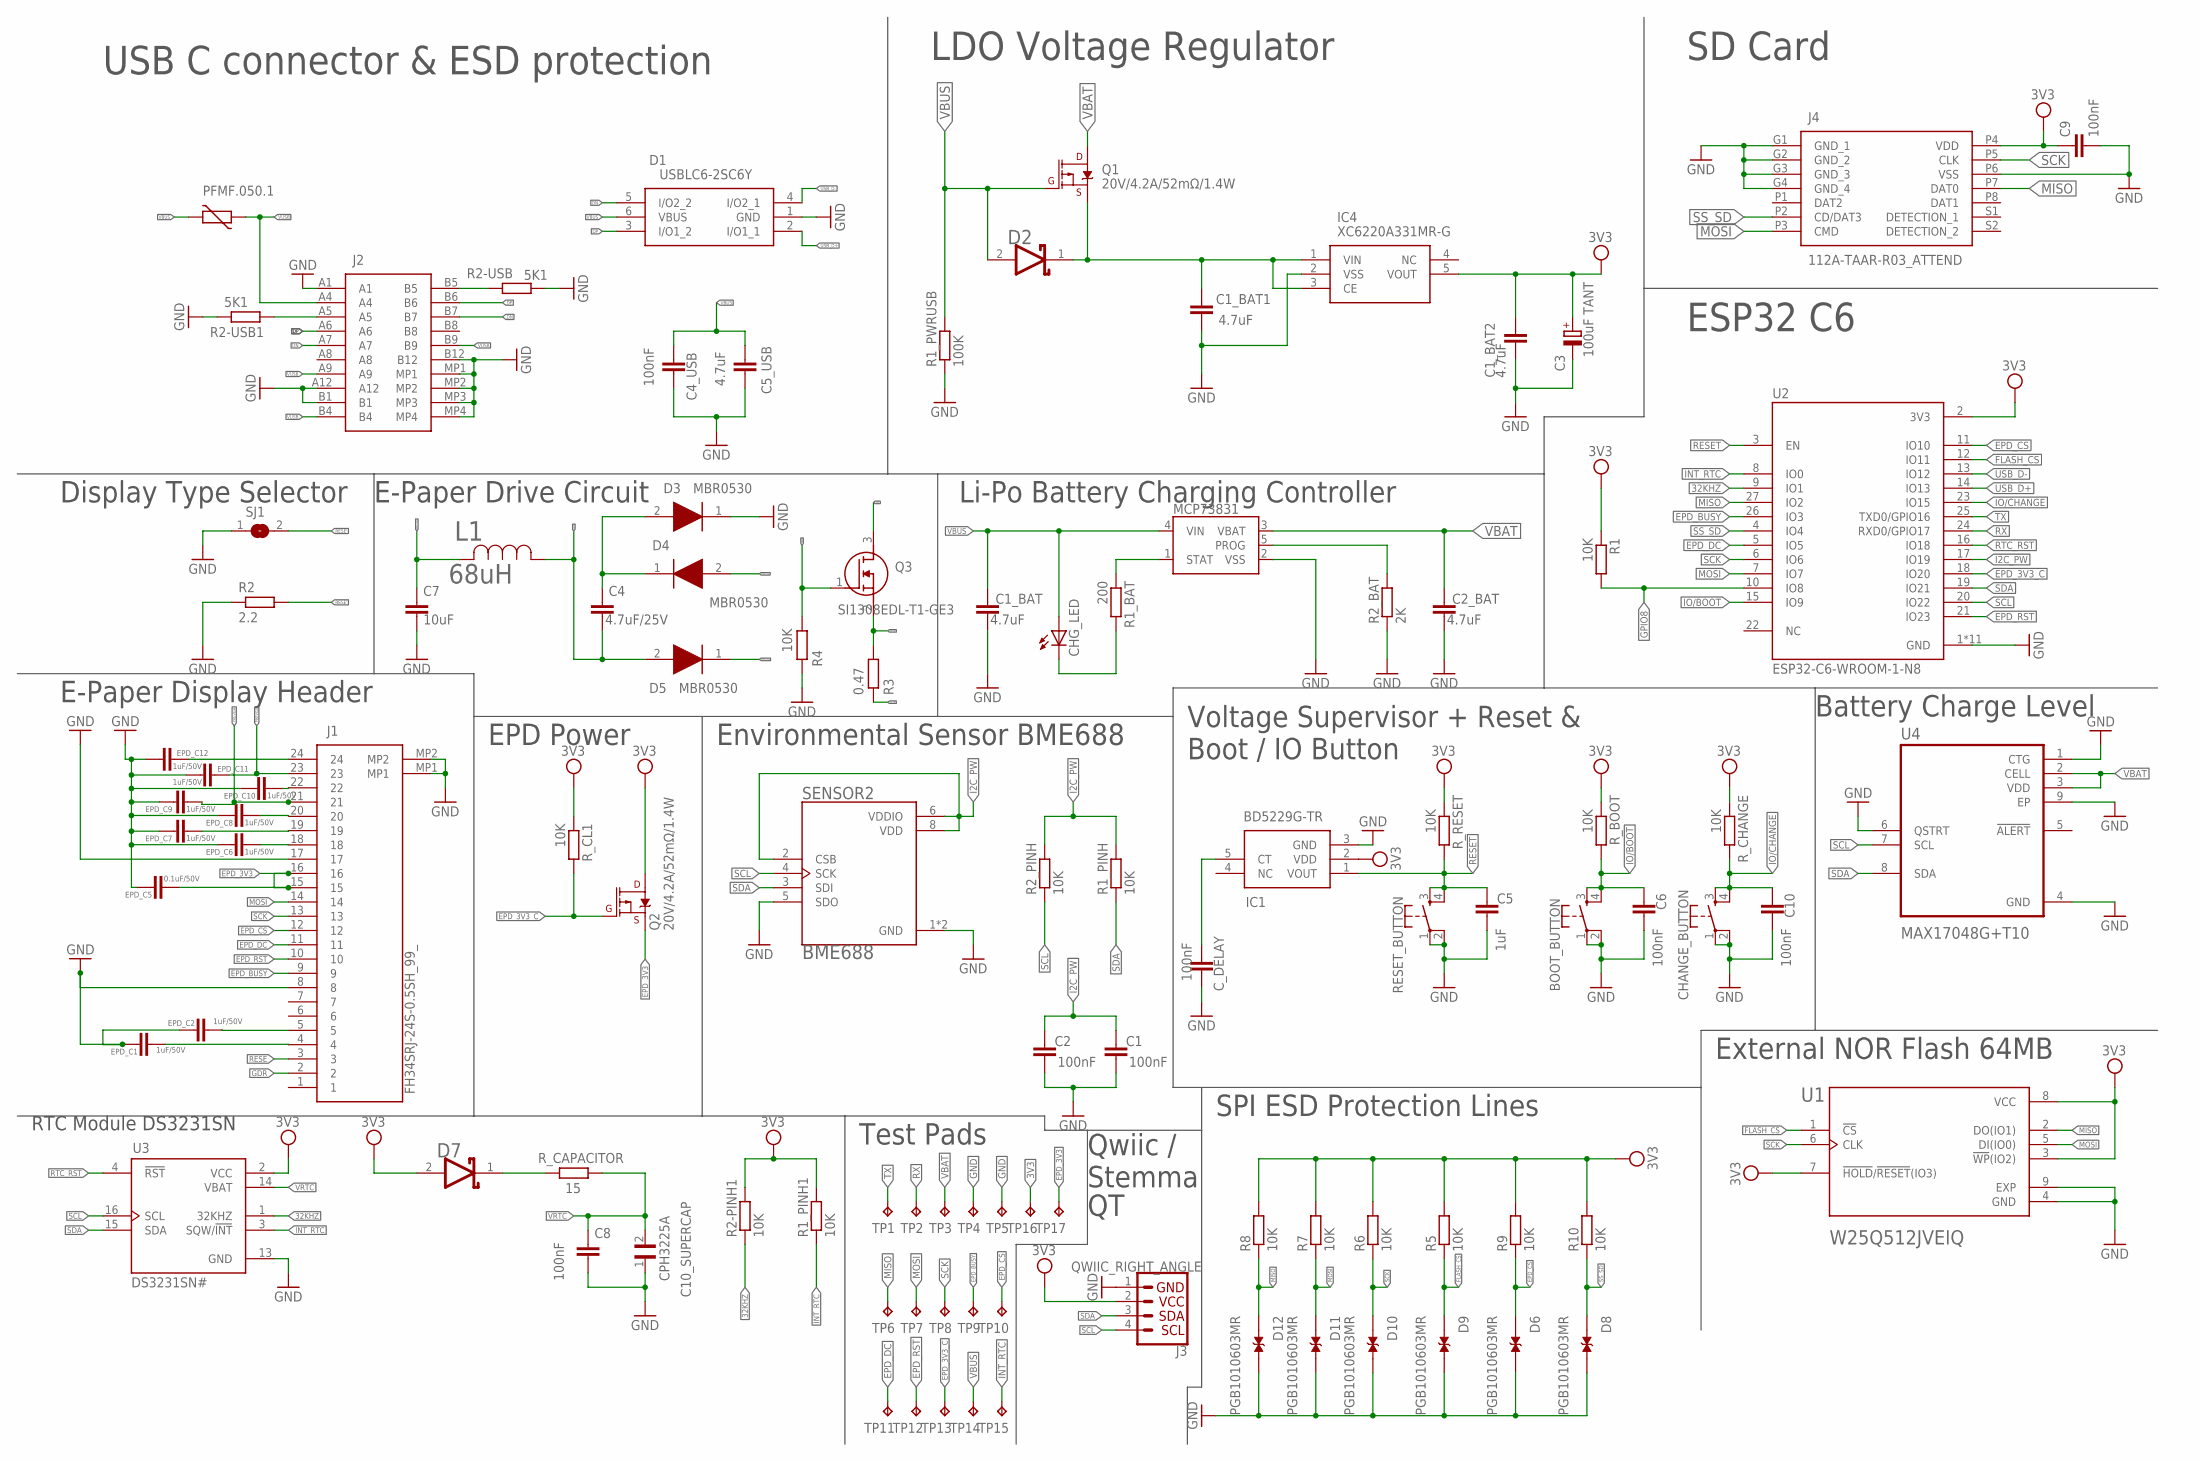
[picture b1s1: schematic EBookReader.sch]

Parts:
BOOT_BUTTON: BUTTON_CUSYOMV1; MYBUTTON
C1, C2, C4_USB, C6, C8, C9, C10: 100nF; EAGLE-LTSPICE_C0402
C1_BAT, C1_BAT1, C1_BAT2, C2_BAT, C5_USB: 4.7uF; EAGLE-LTSPICE_C0402
C3: 100uF TANT; RCL_CT3528
C4: 4.7uF/25V; EAGLE-LTSPICE_C0402
C5: 1uF; EAGLE-LTSPICE_C0402
C7: 10uF; EAGLE-LTSPICE_C0402
C10_SUPERCAP: CPH3225A; CAPCP3225X100N
CHANGE_BUTTON: BUTTON_CUSYOMV1; MYBUTTON
CHG_LED: ADAFRUIT_LEDCHIP-LED0603; ADAFRUIT_CHIP-LED0603
C_DELAY: 100nF; EAGLE-LTSPICE_C0402
D1: USBLC6-2SC6Y; SOT95P280X145-6N
D2, D7: ESP32_WROVER_AVX---SD0805S020S1R0_AVX_SD0805S020S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; ESP32_WROVER_AVX---SD0805S020S1R0_AVX_SD0805S020S1R0_0
D3, D4, D5: MBR0530; SOD3716X135N
D6, D8, D9, D10, D11, D12: PGB1010603MR; DIOC1608X36N
EPD_C1, EPD_C2, EPD_C6, EPD_C7, EPD_C8, EPD_C9, EPD_C10, EPD_C11, EPD_C12: 1uF/50V; EAGLE-LTSPICE_C0402
EPD_C5: 0.1uF/50V; EAGLE-LTSPICE_C0402
IC1: BD5229G-TR; SOT95P280X125-5N
IC4: XC6220A331MR-G; SOT95P280X120-5N
J1: FH34SRJ-24S-0.5SH_99_; FH34SRJ24S05SH99
J2: SAMACSYS_PARTS_USB4110-GF-A; SAMACSYS_PARTS_USB4110GFA
J3: QWIIC_RIGHT_ANGLE; JST04_1MM_RA
J4: 112A-TAAR-R03_ATTEND; 112ATAARR03ATTEND
L1: 68uH; IND_4828-WE-TPC_WRE
MCP73831: ESP32_WROVER_SPARKFUN-IC-POWER_MCP73831; ESP32_WROVER_SPARKFUN-IC-POWER_SOT23-5
PFMF.050.1: ESP32C6_VARISTORCN1812; ESP32C6_VARISTOR_CT/CN1812
Q1, Q2: 20V/4.2A/52mΩ/1.4W; ESP32_WROVER_SPARKFUN-DISCRETESEMI_SOT23-3
Q3: SI1308EDL-T1-GE3; SOT65P210X110-3N
R1, R1_PINH, R1_PINH1, R2-PINH1, R2_PINH, R4, R5, R6, R7, R8, R9, R10: 10K; ESP32_WROVER_EAGLE-LTSPICE_R0402
R1_BAT: 200; ESP32_WROVER_EAGLE-LTSPICE_R0402
R1_PWRUSB: 100K; ESP32_WROVER_EAGLE-LTSPICE_R0402
R2: 2.2; ESP32_WROVER_EAGLE-LTSPICE_R0402
R2-USB, R2-USB1: 5K1; ESP32_WROVER_EAGLE-LTSPICE_R0402
R2_BAT: 2K; ESP32_WROVER_EAGLE-LTSPICE_R0402
R3: 0.47; ESP32_WROVER_EAGLE-LTSPICE_R0402
RESET_BUTTON: BUTTON_CUSYOMV1; MYBUTTON
R_BOOT: 10K; ESP32_WROVER_EAGLE-LTSPICE_R0402
R_CAPACITOR: 15; ESP32_WROVER_EAGLE-LTSPICE_R0402
R_CHANGE: 10K; ESP32_WROVER_EAGLE-LTSPICE_R0402
R_CL1: 10K; ESP32_WROVER_EAGLE-LTSPICE_R0402
R_RESET: 10K; ESP32_WROVER_EAGLE-LTSPICE_R0402
SENSOR2: ESP32_WROVER_BME680_BME680; ESP32_WROVER_BME680_PSON80P300X300X100-8N
SJ1: SJ
TP1, TP2, TP3, TP4, TP5, TP6, TP7, TP8, TP9, TP10, TP11, TP12, TP13, TP14, TP15, TP16, TP17: TPTP20R; TP20R
U1: W25Q512JVEIQ; SON127P600X800X80-9N
U2: ESP32-C6-WROOM-1-N8; XCVR_ESP32-C6-WROOM-1-N8
U3: DS3231SN#; SOIC127P1032X265-16N
U4: MAX17048G+T10; SON50P200X200X80-9N

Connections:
3V3: C1_BAT2.1, C3.+, C9.1, D7.2 (ANODE), IC1.2 (VDD), IC4.5 (VOUT), J3.2, J4.P4 (VDD), Q2.3 (D), R1.1, R1_PINH1.2, R2-PINH1.2, R5.2, R6.2, R7.2, R8.2, R9.2, R10.2, R_BOOT.1, R_CHANGE.1, R_CL1.1, R_RESET.1, TP16.TP, U1.3 (!WP!(IO2)), U1.7 (!HOLD!/!RESET!(IO3)), U1.8 (VCC), U2.2 (3V3), U3.2 (VCC)
32KHZ: R2-PINH1.1, U2.9 (IO1), U3.1 (32KHZ)
DN: D1.5 (I/O2_2), J2.A7, J2.B7
DP: D1.3 (I/O1_2), J2.A6, J2.B6
EPD_3V3: C7.1, EPD_C5.1, J1.15, J1.16, L1.2, Q2.2 (S), TP17.TP
EPD_3V3_C: Q2.1 (G), R_CL1.2, TP13.TP, U2.18 (IO20)
EPD_BUSY: J1.9, TP9.TP, U2.26 (IO3)
EPD_CS: D6.1, J1.12, R9.1, TP10.TP, U2.11 (IO10)
EPD_DC: J1.11, TP11.TP, U2.5 (IO5)
EPD_RST: J1.10, TP12.TP, U2.21 (IO23)
FLASH_CS: D9.1, R5.1, U1.1 (!CS), U2.12 (IO11)
GDR: J1.2, Q3.1 (G), R4.2
GND: BOOT_BUTTON.1, BOOT_BUTTON.2, C1.2, C1_BAT.2, C1_BAT1.2, C1_BAT2.2, C2.2, C2_BAT.2, C3.-, C4_USB.2, C5.2, C5_USB.2, C6.2, C7.2, C8.2, C9.2, C10.2, C10_SUPERCAP.1, CHANGE_BUTTON.1, CHANGE_BUTTON.2, C_DELAY.2, D1.1 (GND), D3.1 (K), D6.2, D8.2, D9.2, D10.2, D11.2, D12.2, EPD_C1.2, EPD_C2.2, EPD_C5.2, EPD_C6.2, EPD_C7.2, EPD_C8.2, EPD_C9.2, EPD_C10.2, EPD_C11.2, EPD_C12.2, IC1.3 (GND), IC4.2 (VSS), J1.8, J1.17, J1.MP1, J1.MP2, J2.A1, J2.A12, J2.B1, J2.B12, J2.MP1, J2.MP2, J2.MP3, J2.MP4, J3.1, J4.G1 (GND_1), J4.G2 (GND_2), J4.G3 (GND_3), J4.G4 (GND_4), J4.P6 (VSS), MCP73831.2 (VSS), R1_PWRUSB.1, R2.1, R2-USB.2, R2-USB1.1, R2_BAT.1, R4.1, RESET_BUTTON.1, RESET_BUTTON.2, SENSOR2.1 (GND), SENSOR2.5 (SDO), SENSOR2.7 (GND), SJ1.1, TP4.TP, TP5.TP, U1.4 (GND), U1.9 (EXP), U2.1 (GND), U2.28 (GND), U2.29_1 (GND), U2.29_2 (GND), U2.29_3 (GND), U2.29_4 (GND), U2.29_5 (GND), U2.29_6 (GND), U2.29_7 (GND), U2.29_8 (GND), U2.29_9 (GND), U3.13 (GND), U4.1 (CTG), U4.4 (GND), U4.6 (QSTRT), U4.9 (EP)
GPIO8: R1.2, U2.10 (IO8)
I2C_PW: C1.1, C2.1, R1_PINH.2, R2_PINH.2, SENSOR2.2 (CSB), SENSOR2.6 (VDDIO), SENSOR2.8 (VDD), U2.17 (IO19)
INT_RTC: R1_PINH1.1, TP15.TP, U2.8 (IO0), U3.3 (SQW/!INT)
IO/BOOT: BOOT_BUTTON.3, BOOT_BUTTON.4, C6.1, R_BOOT.2, U2.15 (IO9)
IO/CHANGE: C10.1, CHANGE_BUTTON.3, CHANGE_BUTTON.4, R_CHANGE.2, U2.23 (IO15)
MISO: D12.1, J4.P7 (DAT0), R8.1, TP6.TP, U1.2 (DO(IO1)), U2.27 (IO2)
MOSI: D11.1, J1.14, J4.P3 (CMD), R7.1, TP7.TP, U1.5 (DI(IO0)), U2.7 (IO7)
unnamed: J2.A5, R2-USB1.2
unnamed: J2.B5, R2-USB.1
unnamed: C4.1, D3.2 (A), D4.1 (K)
unnamed: EPD_C12.1, J1.24
unnamed: EPD_C2.1, J1.5
unnamed: EPD_C10.1, J1.22
unnamed: EPD_C1.1, J1.4
unnamed: EPD_C8.1, J1.20
unnamed: EPD_C6.1, J1.18
unnamed: EPD_C7.1, J1.19
unnamed: D7.1 (CATHODE), R_CAPACITOR.2
unnamed: MCP73831.5 (PROG), R2_BAT.2
unnamed: C1_BAT1.1, D2.1 (CATHODE), IC4.1 (VIN), IC4.3 (CE), Q1.2 (S)
unnamed: CHG_LED.C, R1_BAT.2
unnamed: MCP73831.1 (STAT), R1_BAT.1
unnamed: C_DELAY.1, IC1.5 (CT)
PREVGH: D5.1 (K), EPD_C9.1, J1.21
PREVGL: D4.2 (A), EPD_C11.1, J1.23
RESE: J1.3
RESE': Q3.2 (S), R2.2, R3.1, R3.2, SJ1.2
RESET: C5.1, IC1.1 (VOUT), RESET_BUTTON.3, RESET_BUTTON.4, R_RESET.2, U2.3 (EN)
RTC_RST: U2.16 (IO18), U3.4 (!RST)
RX: TP2.TP, U2.24 (RXD0/GPIO17)
SCK: D10.1, J1.13, J4.P5 (CLK), R6.1, TP8.TP, U1.6 (CLK), U2.6 (IO6)
SCL: J3.4, R2_PINH.1, SENSOR2.4 (SCK), U2.20 (IO22), U3.16 (SCL), U4.7 (SCL)
SDA: J3.3, R1_PINH.1, SENSOR2.3 (SDI), U2.19 (IO21), U3.15 (SDA), U4.8 (SDA)
SRC: C4.2, D5.2 (A), L1.1, Q3.3 (D)
SS_SD: D8.1, J4.P2 (CD/DAT3), R10.1, U2.4 (IO4)
TX: TP1.TP, U2.25 (TXD0/GPIO16)
USB_D+: D1.2 (I/O1_1), U2.14 (IO13)
USB_D-: D1.4 (I/O2_1), U2.13 (IO12)
VBAT: C2_BAT.1, MCP73831.3 (VBAT), Q1.3 (D), TP3.TP, U4.2 (CELL), U4.3 (VDD)
VBUS: C1_BAT.1, C4_USB.1, C5_USB.1, CHG_LED.A, D1.6 (VBUS), D2.2 (ANODE), MCP73831.4 (VIN), Q1.1 (G), R1_PWRUSB.2, TP14.TP
VRTC: C8.1, C10_SUPERCAP.2, R_CAPACITOR.1, U3.14 (VBAT)
VUSB: J2.A4, J2.A9, J2.B4, J2.B9, PFMF.050.1.1

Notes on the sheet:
BME688
USB C connector & ESD protection
Display Type Selector
E-Paper Display Header
RTC Module DS3231SN
E-Paper Drive Circuit
EPD Power
Test Pads
Environmental Sensor BME688
Li-Po Battery Charging Controller
LDO Voltage Regulator
SD Card
ESP32 C6
Voltage Supervisor + Reset & Boot / IO Button
Qwiic / Stemma
SPI ESD Protection Lines
External NOR Flash 64MB
Battery Charge Level

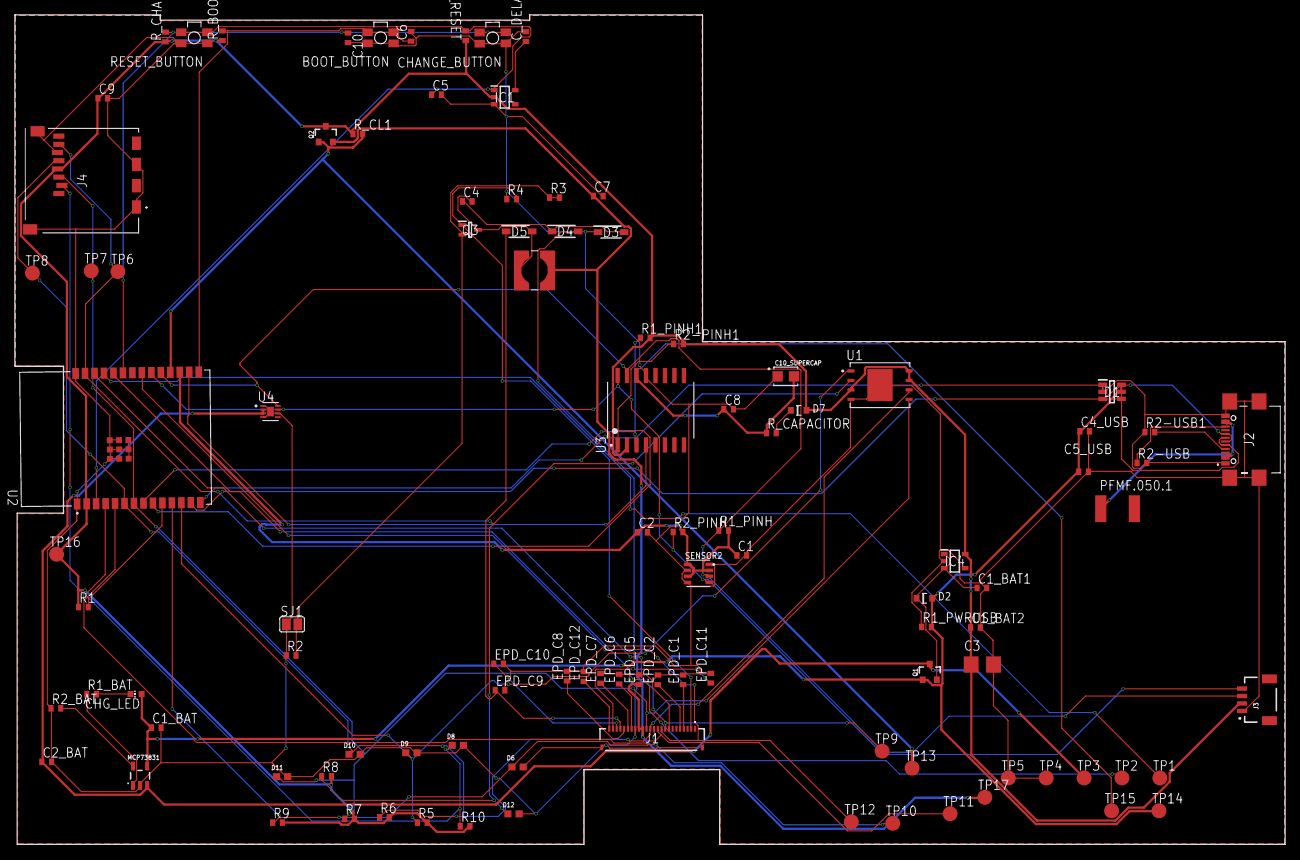
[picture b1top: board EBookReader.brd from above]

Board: 2 copper layers, 170.3 x 111.2 mm, 103 parts (0 on the bottom side), 54 nets.

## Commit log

2025-04-05 Add documents
2025-04-06 Final
2025-04-06 Adaug exploaded view bun
2025-04-15 After review

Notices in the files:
parts and their libraries:
COPYRIGHT: Copyright (C) 2024 Ultra Librarian. All rights reserved.
